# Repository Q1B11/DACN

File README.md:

#Sensorless SPWM BLDC Motor Controller
Design and implement controller for BLDC use SPWM
##Target

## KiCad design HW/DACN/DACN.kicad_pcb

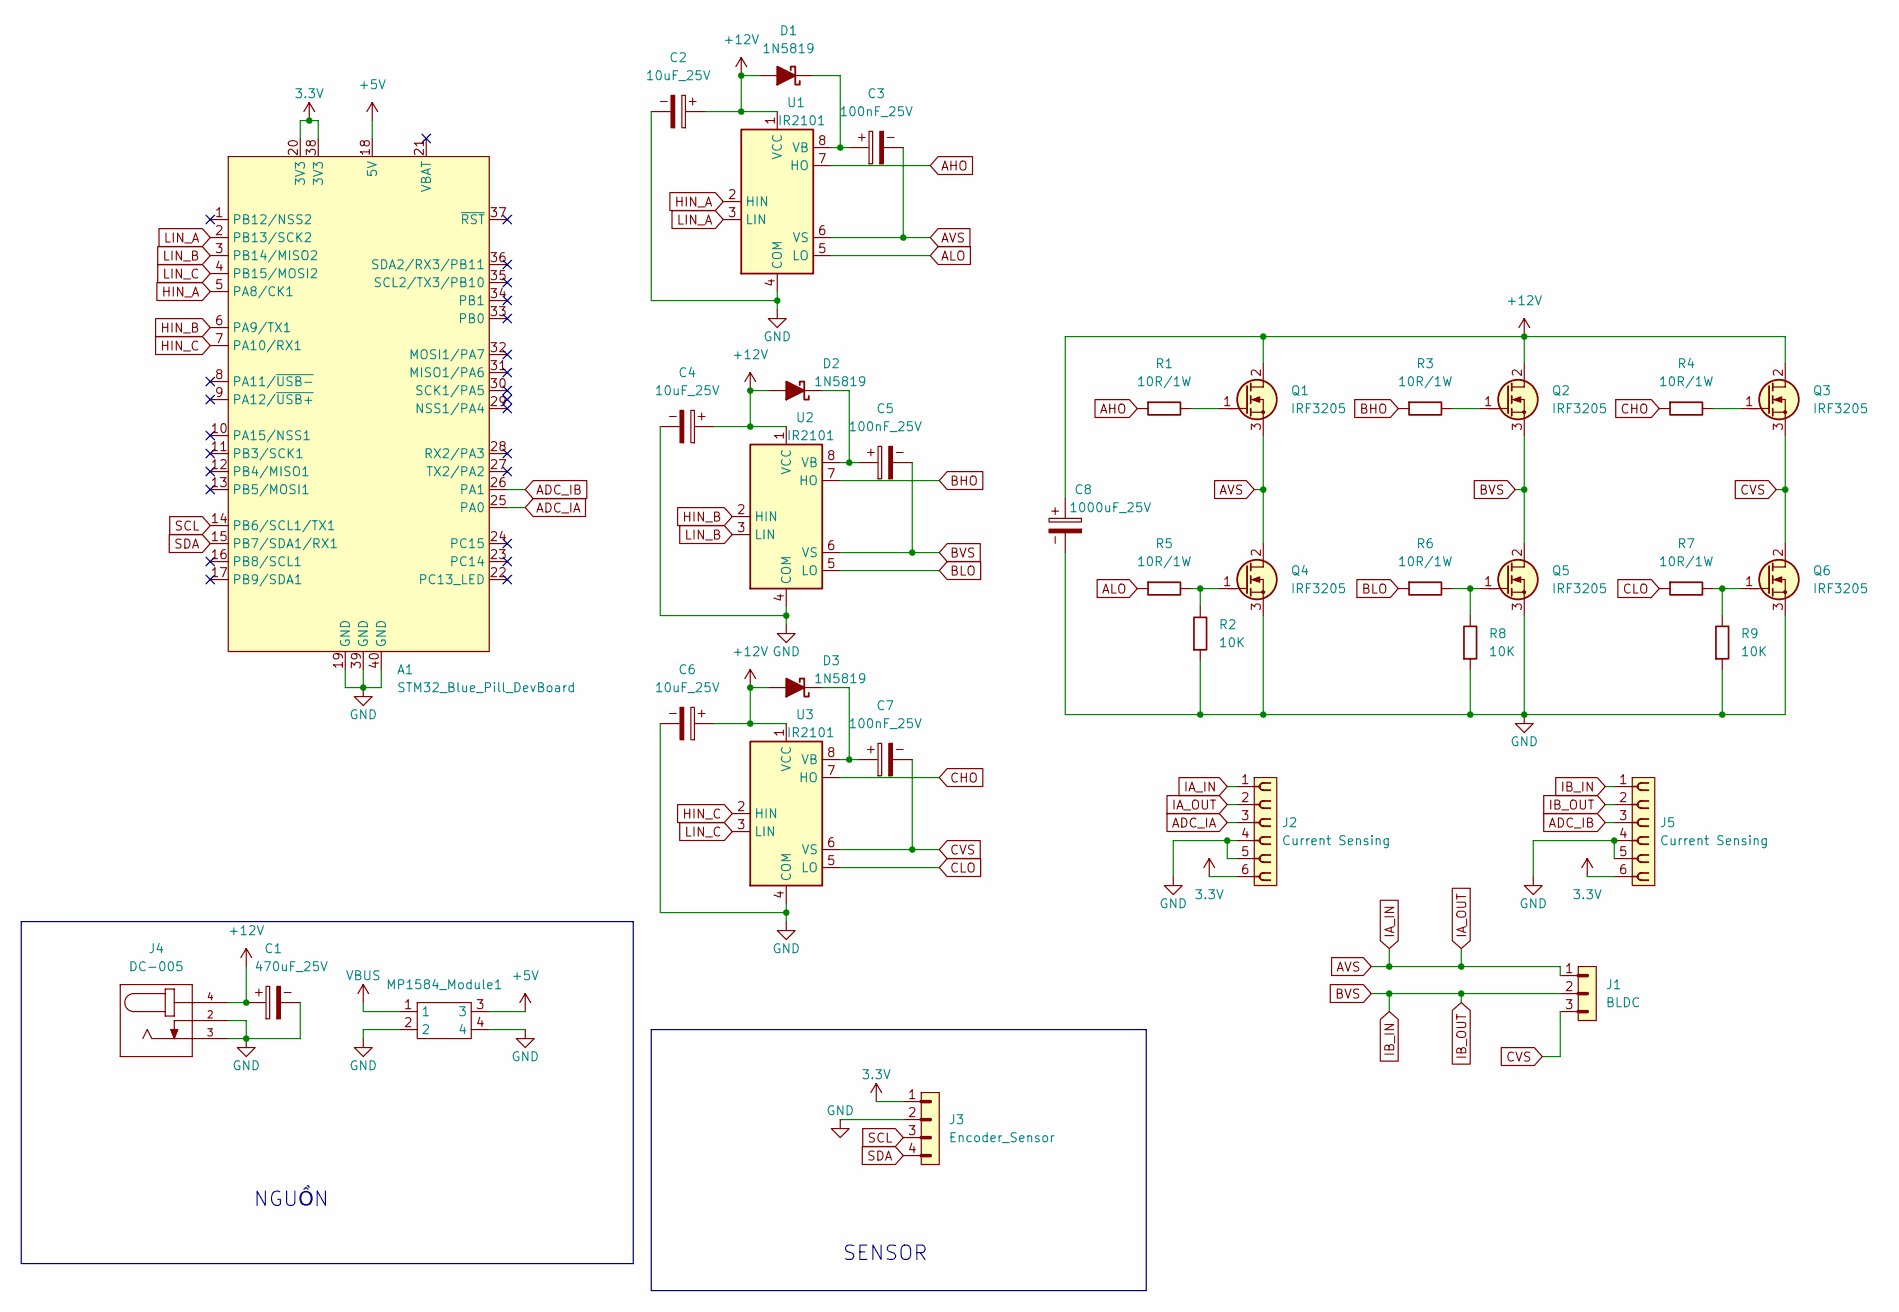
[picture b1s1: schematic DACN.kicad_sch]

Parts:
A1: STM32_Blue_Pill_DevBoard
C1: 470uF_25V; CP_Radial_D8.0mm_P3.50mm
C2, C4, C6: 10uF_25V; CP_Radial_D5.0mm_P2.00mm
C3, C5, C7: 100nF_25V; CP_Radial_D4.0mm_P1.50mm
C8: 1000uF_25V; CP_Radial_D5.0mm_P2.00mm
D1, D2, D3: 1N5819; D_DO-41_SOD81_P7.62mm_Horizontal
J1: BLDC; PinHeader_1x03_P2.54mm_Vertical
J2, J5: Current Sensing; PinSocket_1x06_P2.54mm_Vertical
J3: Encoder_Sensor; PinHeader_1x04_P2.54mm_Vertical
J4: DC-005; NINIGI_DC-005
MP1584_Module1: SRT_MPT1584EN_Module
Q1, Q2, Q3, Q4, Q5, Q6: IRF3205; TO-220-3_Vertical_GDS
R1, R3, R4, R5, R6, R7: 10R/1W; R_Axial_DIN0207_L6.3mm_D2.5mm_P10.16mm_Horizontal
R2, R8, R9: 10K; R_Axial_DIN0207_L6.3mm_D2.5mm_P10.16mm_Horizontal
U1, U2, U3: IR2101; DIP-8_W10.16mm

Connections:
3.3V: A1.20 (3V3), A1.38 (3V3), J2.6, J3.1, J5.6
+5V: A1.18 (5V), MP1584_Module1.3
+12V: C1.1, C2.1, C4.1, C6.1, C8.1, D1.2 (A), D2.2 (A), D3.2 (A), J4.4, Q1.2 (D), Q2.2 (D), Q3.2 (D), U1.1 (VCC), U2.1 (VCC), U3.1 (VCC)
ADC_IA: A1.25 (PA0), J2.3
ADC_IB: A1.26 (PA1), J5.3
AHO: R1.1, U1.7 (HO)
ALO: R5.1, U1.5 (LO)
AVS: C3.2, J1.1, J2.1, J2.2, Q1.3 (S), Q4.2 (D), U1.6 (VS)
BHO: R3.1, U2.7 (HO)
BLO: R6.1, U2.5 (LO)
BVS: C5.2, J1.2, J5.1, J5.2, Q2.3 (S), Q5.2 (D), U2.6 (VS)
CHO: R4.1, U3.7 (HO)
CLO: R7.1, U3.5 (LO)
CVS: C7.2, J1.3, Q3.3 (S), Q6.2 (D), U3.6 (VS)
GND: A1.19 (GND), A1.39 (GND), A1.40 (GND), C1.2, C2.2, C4.2, C6.2, C8.2, J2.4, J2.5, J3.2, J4.2, J4.3, J5.4, J5.5, MP1584_Module1.2, MP1584_Module1.4, Q4.3 (S), Q5.3 (S), Q6.3 (S), R2.1, R8.1, R9.1, U1.4 (COM), U2.4 (COM), U3.4 (COM)
HIN_A: A1.5 (PA8/CK1), U1.2 (HIN)
HIN_B: A1.6 (PA9/TX1), U2.2 (HIN)
HIN_C: A1.7 (PA10/RX1), U3.2 (HIN)
LIN_A: A1.2 (PB13/SCK2), U1.3 (LIN)
LIN_B: A1.3 (PB14/MISO2), U2.3 (LIN)
LIN_C: A1.4 (PB15/MOSI2), U3.3 (LIN)
unnamed: C3.1, D1.1 (K), U1.8 (VB)
unnamed: C5.1, D2.1 (K), U2.8 (VB)
unnamed: C7.1, D3.1 (K), U3.8 (VB)
unnamed: Q1.1 (G), R1.2
unnamed: Q2.1 (G), R3.2
unnamed: Q3.1 (G), R4.2
unnamed: Q4.1 (G), R2.2, R5.2
unnamed: Q5.1 (G), R6.2, R8.2
unnamed: Q6.1 (G), R7.2, R9.2
SCL: A1.14 (PB6/SCL1/TX1), J3.3
SDA: A1.15 (PB7/SDA1/RX1), J3.4
VBUS: MP1584_Module1.1

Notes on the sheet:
SENSOR
NGUỒN

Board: 2 copper layers, 36 parts (0 on the bottom side), 32 nets, no tracks yet.

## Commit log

2026-05-26 Modified Power&MCU
2026-05-26 Change power 3.3v to power
2026-05-28 add driver and mosfet
2026-06-01 Add connectors,..
2026-06-01 Add initial README with project title
2026-06-02 change dicrectory
2026-06-04 change
2026-06-13 add source and buck converter
